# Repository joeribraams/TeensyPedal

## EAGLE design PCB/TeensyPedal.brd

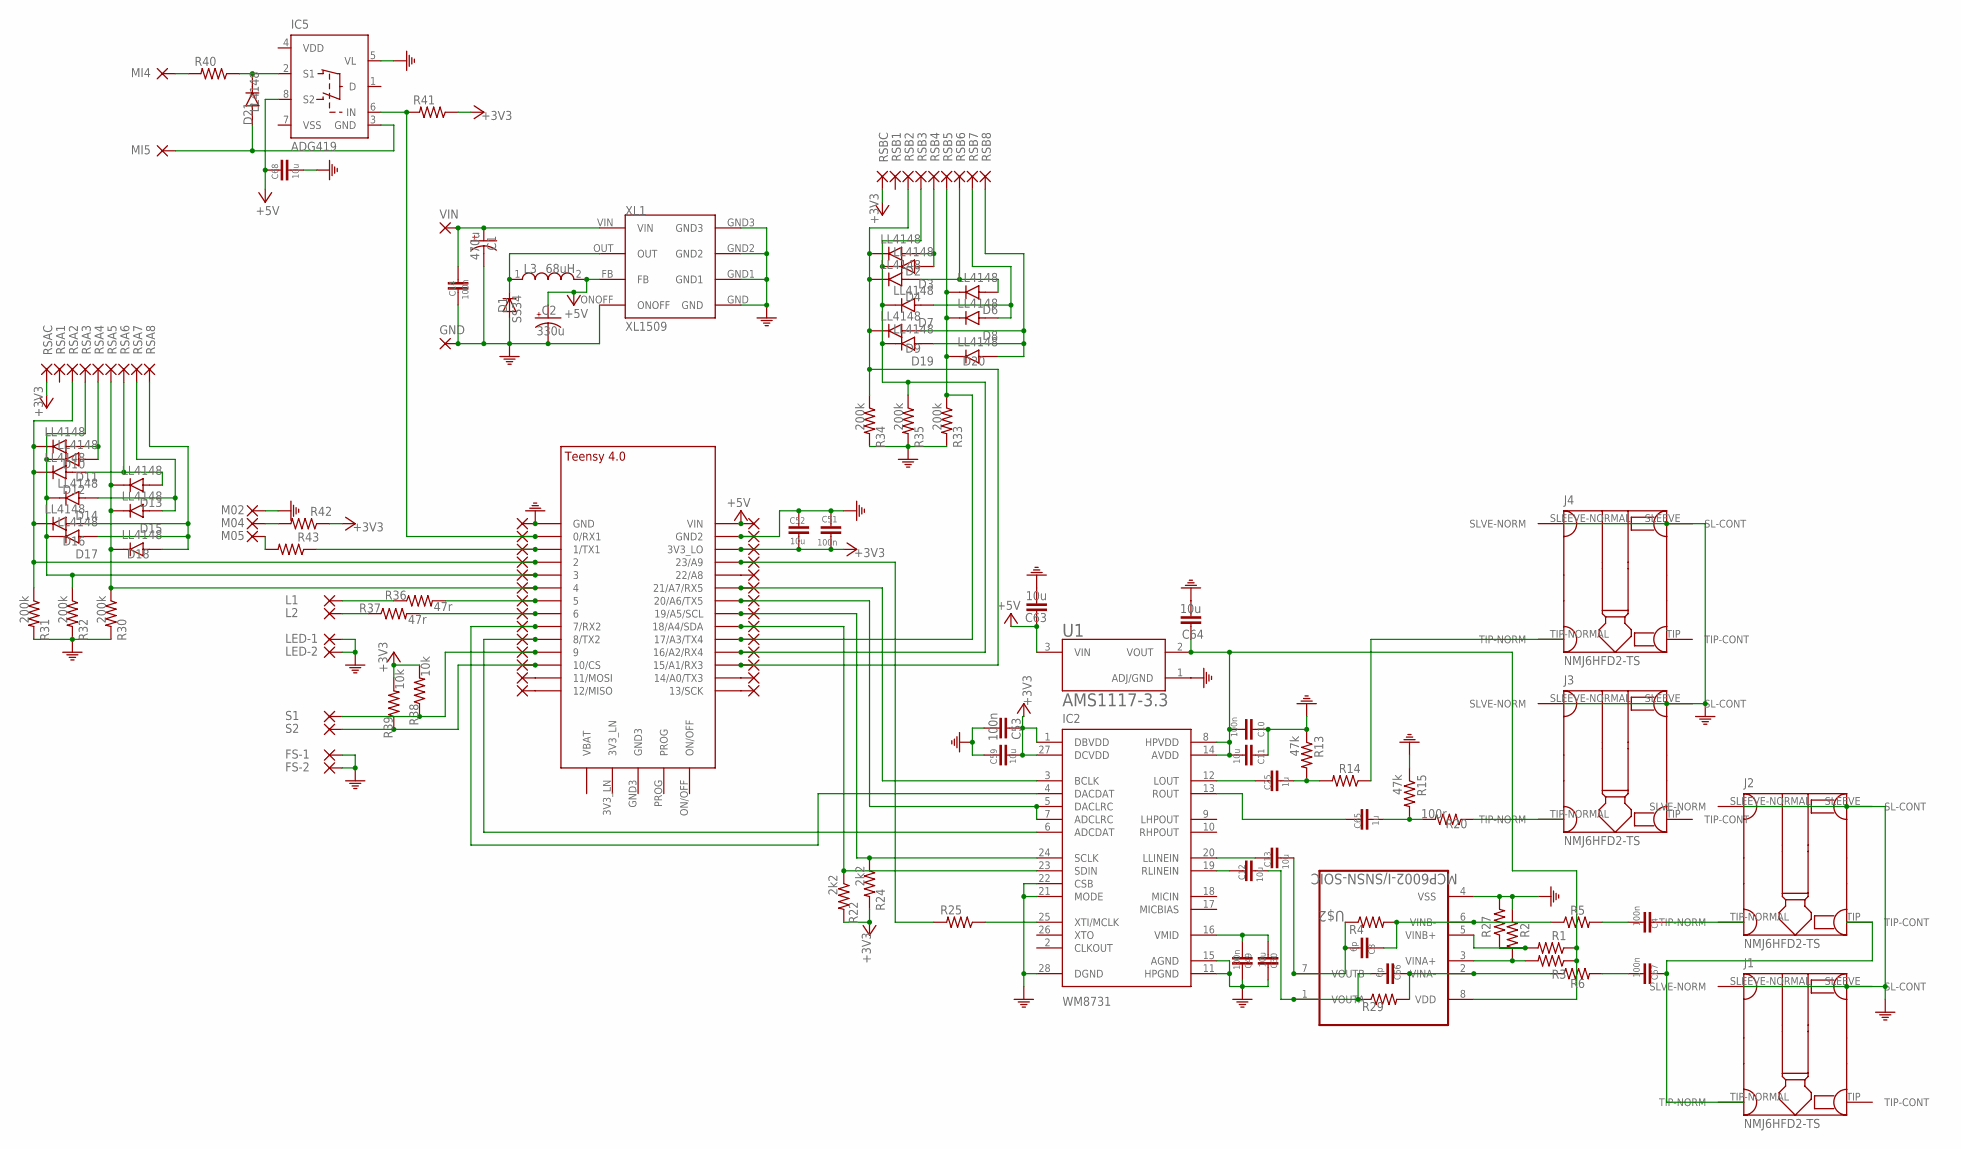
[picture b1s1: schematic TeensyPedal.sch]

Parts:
+5V: 1,6/0,9
C1: 470u; B45181B
C2: 330u; B45181B
C3, C66: 6p; C0603
C4, C10, C14, C49, C51, C53, C67: 100n; C0603
C11, C12, C13, C30, C52, C59, C63, C64, C68: 10u; C0805
C25, C65: 1u; C0603
D1: SS34; DO214AC
D2, D3, D4, D6, D7, D8, D9, D10, D11, D12, D13, D14, D15, D16, D17, D18, D19, D20, D21: LL4148; DIO_LL4148
FS-1, FS-2: 1,6/0,9
GND: 1,6/0,9
GND10: 2,15/1,0
IC2: WM8731; SSOP28
IC5: ADG419; DIL08
J1, J2, J3, J4: NMJ6HFD2-TS
L1, L2: 1,6/0,9
L3: 68uH; WE-PD_1260/1245/1280/1210
LED-1, LED-2: 1,6/0,9
M02, M04, M05: 2,15/1,0
MI4, MI5: 2,15/1,0
PIN, PIN1, PIN2, PIN3, PIN4, PIN5, PIN6, PIN7, PIN8, PIN9, PIN10, PIN11, PIN12, PIN13, PIN14, PIN15, PIN16, PIN17, PIN18, PIN19, PIN20, PIN21, PIN22, PIN23, PIN24, PIN25: 1,6/0,9
R1, R2, R3, R27, R30, R31, R32, R33, R34, R35: 200k; R0603
R4, R29: 1m; 0204/7
R5, R6: 1m; R0603
R13, R15: 47k; R0603
R14, R20: 100r; R0603
R22, R24: 2k2; R0603
R25, R40: 220r; R0603
R36, R37, R42, R43: 47r; R0603
R38, R39: 10k; R0603
R41: 470r; R0603
RSA1, RSA2, RSA3, RSA4, RSA5, RSA6, RSA7, RSA8: 2,15/1,0
RSAC: 2,15/1,0
RSB1: 2,54/1,1
RSB2, RSB3, RSB4, RSB5, RSB6, RSB7, RSB8: 2,15/1,0
RSBC: 2,15/1,0
S1, S2: 1,6/0,9
U1: AMS1117-3.3; SOT229P700X180-4N
U$1: TEENSY_4.0
U$2: MCP6002-I/SNSN-SOIC; SOIC127P690X150-8N
VIN: 2,15/1,0
XL1: XL1509

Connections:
3V3_ANA1: C10.1, C11.1, C64.1, IC2.8 (HPVDD), IC2.14 (AVDD), R1.1, R3.1, U1.2 (VOUT), U$2.8 (VDD)
+3V3: C51.1, C52.2, C53.1, C59.2, IC2.1 (DBVDD), IC2.27 (DCVDD), PIN24.1, R22.2, R24.2, R38.2, R39.2, R41.1, R42.1, RSAC.1, RSBC.1, U$1.3V3_LO
+5V: +5V.1, C2.+, C63.1, C68.1, IC5.8 (S2), L3.2, U1.3 (VIN), U$1.VIN, XL1.FB
unnamed: D1.C, L3.1, XL1.OUT
unnamed: C30.2, C49.2, IC2.16 (VMID)
unnamed: IC2.24 (SCLK), PIN19.1, R24.1, U$1.19/A5/SCL
unnamed: IC2.23 (SDIN), PIN18.1, R22.1, U$1.18/A4/SDA
unnamed: C4.2, J2.TIP-NORMAL (TIP-NORM)
unnamed: R1.2, R27.1, U$2.5 (VINB+)
unnamed: C4.1, R5.2
unnamed: C12.1, C66.1, R29.1, U$2.1 (VOUTA)
unnamed: R2.1, R3.2, U$2.3 (VINA+)
unnamed: C3.2, R4.2, R5.1, U$2.6 (VINB-)
unnamed: C66.2, R6.1, R29.2, U$2.2 (VINA-)
unnamed: C3.1, C13.1, R4.1, U$2.7 (VOUTB)
unnamed: C67.1, R6.2
unnamed: C67.2, J1.TIP-NORMAL (TIP-NORM), J2.TIP (TIP-CONT)
unnamed: PIN13.1, U$1.13/SCK
unnamed: IC2.5 (DACLRC), IC2.7 (ADCLRC), PIN20.1, U$1.20/A6 (20/A6/TX5)
unnamed: PIN14.1, U$1.14/A0 (14/A0/TX3)
unnamed: C25.1, R13.2, R14.2
unnamed: C25.2, IC2.12 (LOUT)
unnamed: J4.TIP-NORMAL (TIP-NORM), R14.1
unnamed: C65.1, R15.2, R20.2
unnamed: J3.TIP-NORMAL (TIP-NORM), R20.1
unnamed: C65.2, IC2.13 (ROUT)
unnamed: IC2.4 (DACDAT), PIN7.1, U$1.7 (7/RX2)
unnamed: IC2.6 (ADCDAT), PIN8.1, U$1.8 (8/TX2)
unnamed: IC2.3 (BCLK), PIN21.1, U$1.21/A7 (21/A7/RX5)
unnamed: PIN23.1, R25.2, U$1.23/A9
unnamed: IC2.25 (XTI/MCLK), R25.1
unnamed: C13.2, IC2.20 (LLINEIN)
unnamed: D10.A, D11.A, RSA4.1
unnamed: C12.2, IC2.19 (RLINEIN)
unnamed: D12.A, D13.A, RSA6.1
unnamed: D14.A, D15.A, RSA7.1
unnamed: D16.A, D17.A, D18.A, RSA8.1
unnamed: IC5.6 (IN), PIN.1, R41.2, U$1.0/RX (0/RX1)
unnamed: PIN1.1, R43.1, U$1.1/TX (1/TX1)
unnamed: PIN5.1, R36.2, U$1.5
unnamed: PIN6.1, R37.2, U$1.6
unnamed: D21.C, IC5.2 (S1), R40.1
unnamed: D21.A, IC5.3 (GND), MI5.1
unnamed: PIN11.1, U$1.11/MOSI
unnamed: PIN12.1, U$1.12/MISO
unnamed: L1.1, R36.1
unnamed: L2.1, R37.1
unnamed: MI4.1, R40.2
unnamed: PIN22.1, U$1.22/A8
unnamed: D2.A, D3.A, RSB4.1
unnamed: D4.A, D6.A, RSB6.1
unnamed: D7.A, D8.A, RSB7.1
unnamed: D9.A, D19.A, D20.A, RSB8.1
unnamed: PIN9.1, R38.1, S1.1, U$1.9/CS (9)
unnamed: PIN10.1, R39.1, S2.1, U$1.10/CS
unnamed: M04.1, R42.2
unnamed: M05.1, R43.2
PE: C1.-, C2.-, C10.2, C11.2, C14.1, C30.1, C49.1, C51.2, C52.1, C53.2, C59.1, C63.2, C64.2, C68.2, D1.A, FS-1.1, FS-2.1, GND.1, GND10.1, IC2.11 (HPGND), IC2.15 (AGND), IC2.21 (MODE), IC2.22 (CSB), IC2.28 (DGND), IC5.5 (VL), J1.SLEEVE (SL-CONT), J1.SLEEVE-NORMAL (SLVE-NORM), J2.SLEEVE (SL-CONT), J2.SLEEVE-NORMAL (SLVE-NORM), J3.SLEEVE (SL-CONT), J3.SLEEVE-NORMAL (SLVE-NORM), J4.SLEEVE (SL-CONT), J4.SLEEVE-NORMAL (SLVE-NORM), LED-1.1, LED-2.1, M02.1, PIN25.1, R2.2, R13.1, R15.1, R27.2, R30.2, R31.2, R32.2, R33.2, R34.2, R35.2, U1.1 (ADJ/GND), U$1.GND, U$1.GND2, U$2.4 (VSS), XL1.GND, XL1.GND1, XL1.GND2, XL1.GND3, XL1.ONOFF
RSW1: D10.C, D12.C, D16.C, PIN2.1, R31.1, RSA2.1, U$1.2
RSW2: D11.C, D14.C, D17.C, PIN3.1, R32.1, RSA3.1, U$1.3/CANTX (3)
RSW3: D13.C, D15.C, D18.C, PIN4.1, R30.1, RSA5.1, U$1.4/CANRX (4)
RSW4: D6.C, D8.C, D20.C, PIN17.1, R33.1, RSB5.1, U$1.17/A3 (17/A3/TX4)
RSW5: D3.C, D7.C, D19.C, PIN16.1, R35.1, RSB3.1, U$1.16/A2 (16/A2/RX4)
RSW6: D2.C, D4.C, D9.C, PIN15.1, R34.1, RSB2.1, U$1.15/A1 (15/A1/RX3)
VDD: IC5.4 (VDD)
VIN: C1.+, C14.2, VIN.1, XL1.VIN
VSS: IC5.7 (VSS)

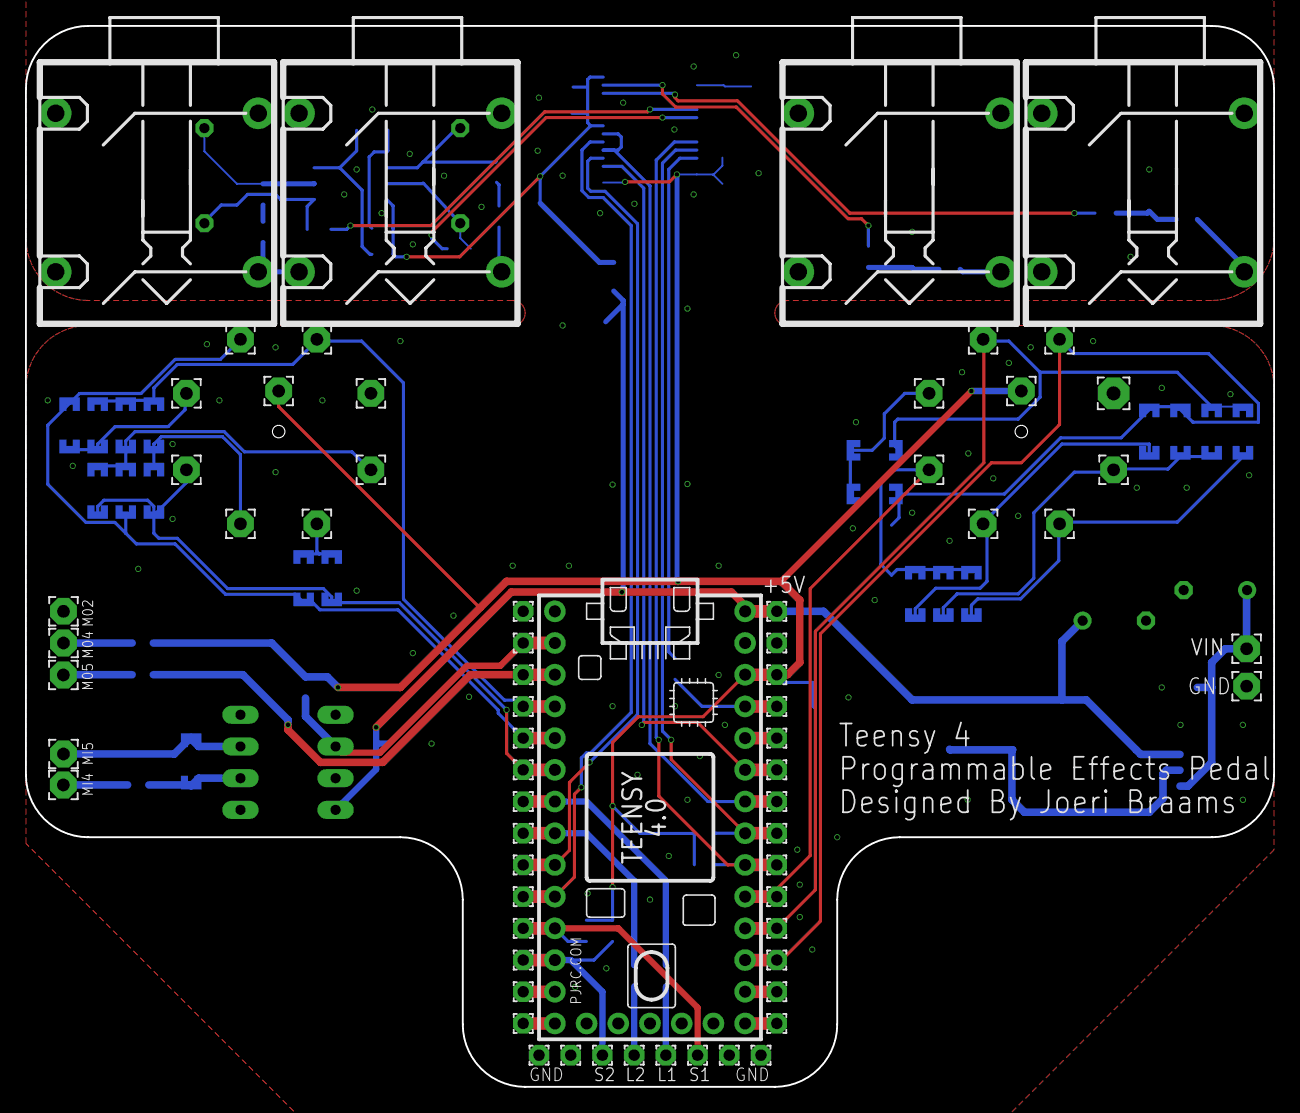
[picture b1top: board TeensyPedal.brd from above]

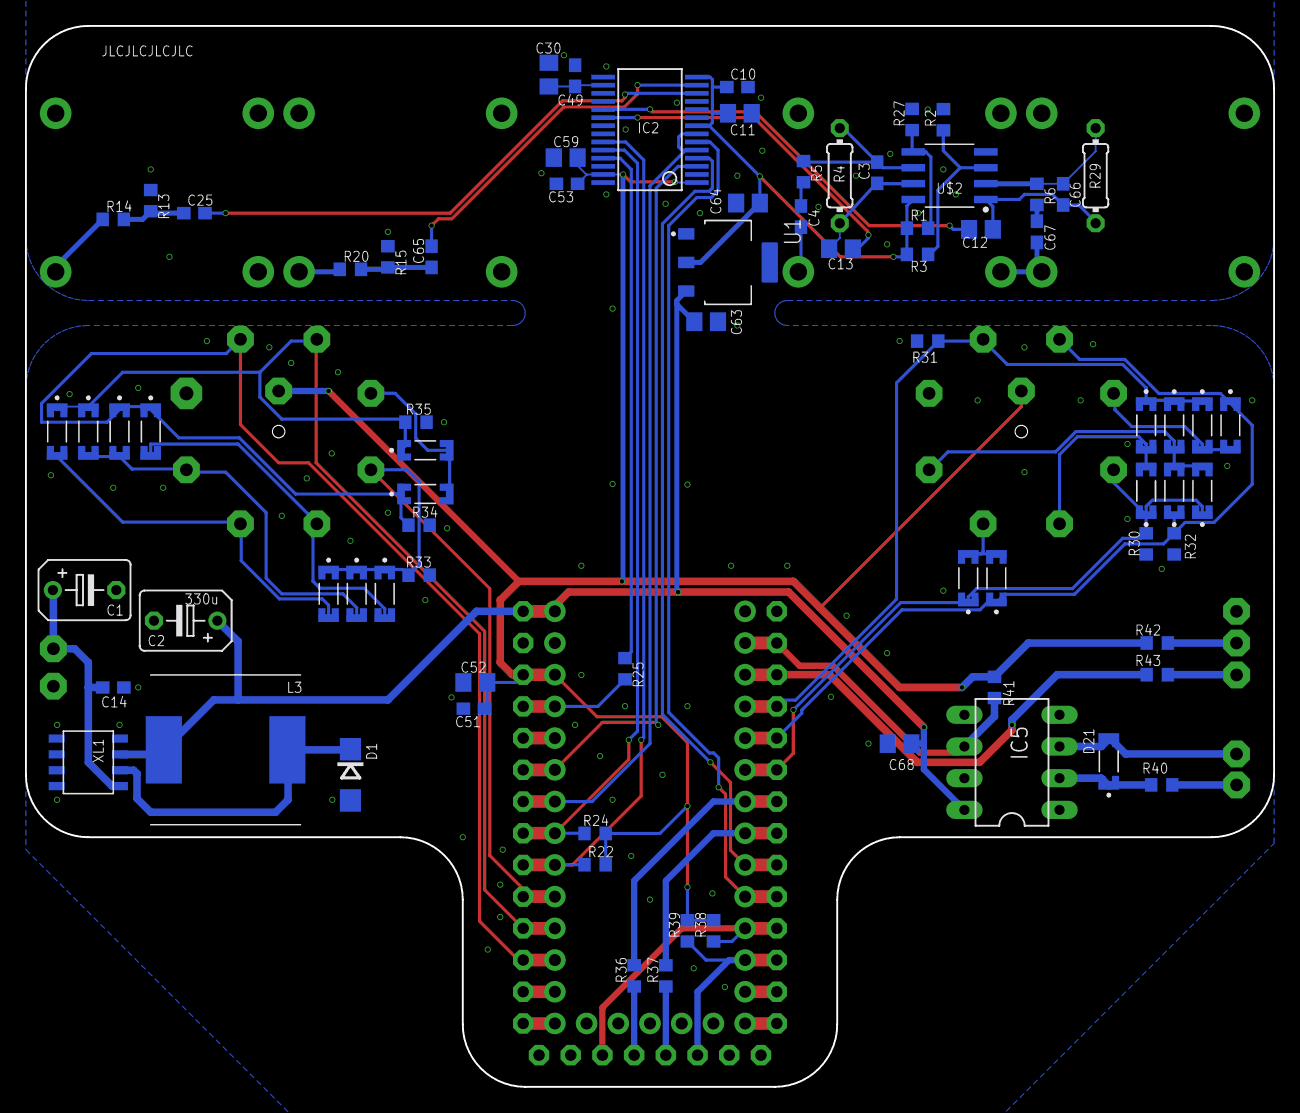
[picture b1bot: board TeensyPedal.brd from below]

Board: 2 copper layers, 100.0 x 85.0 mm, 143 parts (77 on the bottom side), 65 nets.

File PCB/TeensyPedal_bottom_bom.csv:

Comment,Designator,Footprint,LCSC Part #
,,,
6p,C3 C66,C0603,C37474
100n,C4 C10 C14 C49 C51 C53 C67,C0603,C14663
1u,C25 C65,C0603,C15849
10u,C11 C12 C13 C30 C52 C59 C63 C64 C68,C0805,C15850
,,,
47r,R36 R37 R42 R43,R0603,C23182
100r,R14 R20,R0603,C22775
220r,R25 R40,R0603,C22962
470r,R41,R0603,C23179
2k2,R22 R24,R0603,C4190
10k,R38 R39,R0603,C25804
47k,R13 R15,R0603,C25819
200k,R1 R2 R3 R27 R30 R31 R32 R33 R34 R35,R0603,C25811
1m,R5 R6,R0603,C22935
,,,
SS34,D1,"SMA,DO-214AC",C8678
LL4148,D2 D3 D4 D6 D7 D8 D9 D10 D11 D12 D13 D14 D15 D16 D17 D18 D19 D20 D21,LL-34,C9808
,,,
68uH,L3,SMD-PIND-12.5x12.5x5_2.9x5.4,C169399
,,,
XL1509,XL1,SOP-8_3.9x4.9x1.27P,C74193
AMS1117-3.3,U1,SOT229P700X180-4N, C6186
,,,
MCP6002-I/SN,U$2,SOIC-8_3.9x4.9x1.27P,C7377
,,,
WM8731,IC2,SSOP-28_5.3x10.2x0.65P,C323837

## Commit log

2020-12-22 Initial Commit, (imperfect, but finished) PCB files and beginning of code
2020-12-23 Fixed EXTMEM
2020-12-24 Added Feedbacker
2020-12-26 Added USB audio, Added Reverse
2021-02-17 Update FXLooper.h
    tweaked Looper

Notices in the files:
parts and their libraries:
Wurth_Elektronik_Passive_rev15e: Copyright: Würth Elektronik
